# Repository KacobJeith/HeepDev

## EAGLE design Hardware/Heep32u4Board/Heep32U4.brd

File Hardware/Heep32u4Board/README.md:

# ATMega32u4 Board

### Description

This circuit board is designed to communicate with a Heep system without the need for any Arduino or Teensy circuit boards. It contains 2 relays, an ATMega32u4 Processor, and an ENC28J60 Ethernet Controller

### Schematic

### Layout

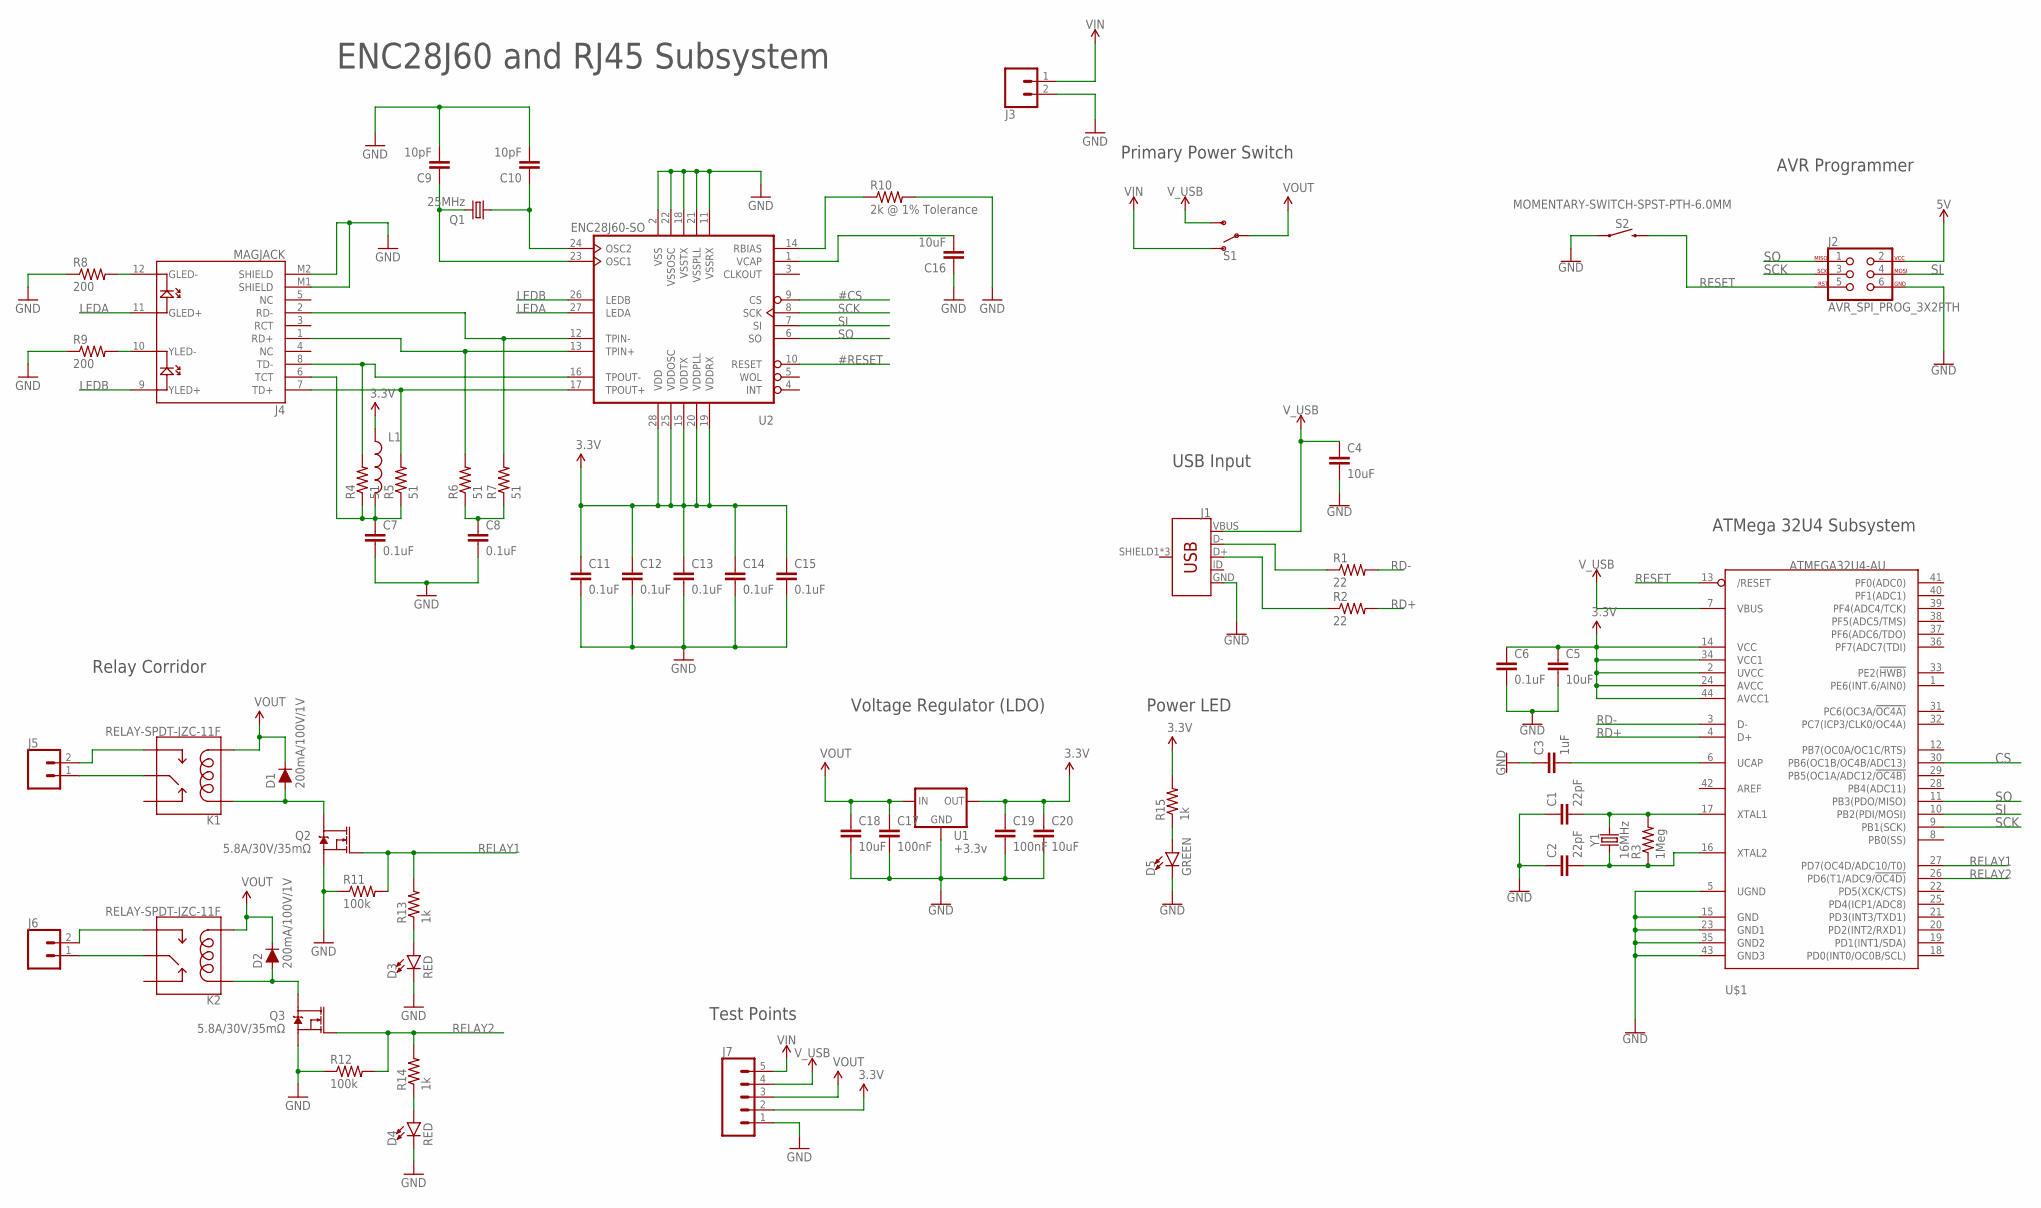
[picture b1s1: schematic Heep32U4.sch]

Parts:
C1, C2: 22pF; 0603-CAP
C3: 1uF; 0603-CAP
C4, C5, C16, C18, C20: 10uF; 0603-CAP
C6, C7, C8, C11, C12, C13, C14, C15: 0.1uF; 0603-CAP
C9, C10: 10pF; 0603-CAP
C17, C19: 100nF; 0603-CAP
D1, D2: 200mA/100V/1V; DIODE-1N4148
D3, D4: RED; LED-0603
D5: GREEN; LED-0603
J1: USB_MICRO-B_FEMALE-SMT; USB-B-MICRO-SMD
J2: AVR_SPI_PROG_3X2PTH; 2X3
J3: CONN_02; 1X02
J4: MAGJACK
J5, J6: CONN_025MM; SCREWTERMINAL-5MM-2
J7: CONN_05; 1X05
K1, K2: RELAY-SPDT-JZC-11F; RELAY-JZC
L1: INDUCTOR0603; 0603
Q1: 25MHz; SM49
Q2, Q3: 5.8A/30V/35mΩ; SOT23-3
R1, R2: 22; 0603-RES
R3: 1Meg; 0603-RES
R4, R5, R6, R7: 51; 0603-RES
R8, R9: 200; 0603-RES
R10: 2k @ 1% Tolerance; 0603-RES
R11, R12: 100k; 0603-RES
R13, R14, R15: 1k; 0603-RES
S1: SWITCH-SPDT-PTH-11.6X4.0MM; SWITCH_SPDT_PTH_11.6X4.0MM
S2: MOMENTARY-SWITCH-SPST-PTH-6.0MM; TACTILE_SWITCH_PTH_6.0MM
U1: +3.3v; TO-252
U2: ENC28J60-SO; SO28W
U$1: ATMEGA32U4-AU; TQFP44
Y1: 16MHz; HC49UP

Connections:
3.3V: C5.1, C6.1, C11.1, C12.1, C13.1, C14.1, C15.1, C19.1, C20.1, J7.2, L1.1, R15.2, U1.2 (OUT), U2.15 (VDDTX), U2.19 (VDDRX), U2.20 (VDDPLL), U2.25 (VDDOSC), U2.28 (VDD), U$1.2 (UVCC), U$1.14 (VCC), U$1.24 (AVCC), U$1.34 (VCC1), U$1.44 (AVCC1)
5V: J2.2
#CS: U2.9 (CS)
#RESET: U2.10 (RESET)
CS: U$1.30 (PB6(OC1B/OC4B/ADC13))
GND: C1.1, C2.1, C3.1, C4.2, C5.2, C6.2, C7.2, C8.2, C9.2, C10.2, C11.2, C12.2, C13.2, C14.2, C15.2, C16.1, C17.2, C18.2, C19.2, C20.2, D3.C, D4.C, D5.C, J1.GND, J2.6, J3.2, J4.M1 (SHIELD), J4.M2 (SHIELD), J7.1, Q2.2 (S), Q3.2 (S), R8.1, R9.1, R10.2, R11.1, R12.1, S2.1, U1.3 (GND), U2.2 (VSS), U2.11 (VSSRX), U2.18 (VSSTX), U2.21 (VSSPLL), U2.22 (VSSOSC), U$1.5 (UGND), U$1.15 (GND), U$1.23 (GND1), U$1.35 (GND2), U$1.43 (GND3)
LEDA: J4.11 (GLED+), U2.27 (LEDA)
LEDB: J4.9 (YLED+), U2.26 (LEDB)
unnamed: C3.2, U$1.6 (UCAP)
unnamed: J4.1 (RD+), R6.2, U2.13 (TPIN+)
unnamed: J1.D-, R1.1
unnamed: J1.D+, R2.1
unnamed: J4.2 (RD-), R7.2, U2.12 (TPIN-)
unnamed: J4.8 (TD-), R4.2, U2.16 (TPOUT-)
unnamed: J4.7 (TD+), R5.2, U2.17 (TPOUT+)
unnamed: C8.1, R6.1, R7.1
unnamed: C1.2, R3.2, U$1.17 (XTAL1), Y1.2
unnamed: C2.2, R3.1, U$1.16 (XTAL2), Y1.1
unnamed: C7.1, J4.6 (TCT), L1.2, R4.1, R5.1
unnamed: J4.10 (YLED-), R9.2
unnamed: J4.12 (GLED-), R8.2
unnamed: C9.1, Q1.2, U2.23 (OSC1)
unnamed: C10.1, Q1.1, U2.24 (OSC2)
unnamed: R10.1, U2.14 (RBIAS)
unnamed: C16.2, U2.1 (VCAP)
unnamed: J5.2, K1.3 (NO)
unnamed: J5.1, K1.4 (MAIN)
unnamed: J6.2, K2.3 (NO)
unnamed: J6.1, K2.4 (MAIN)
unnamed: D2.A, K2.5 (COIL1), Q3.3 (D)
unnamed: D1.A, K1.5 (COIL1), Q2.3 (D)
unnamed: D5.A, R15.1
unnamed: D4.A, R14.1
unnamed: D3.A, R13.1
RD+: R2.2, U$1.4 (D+)
RD-: R1.2, U$1.3 (D-)
RELAY1: Q2.1 (G), R11.2, R13.2, U$1.27 (PD7(OC4D/ADC10/T0))
RELAY2: Q3.1 (G), R12.2, R14.2, U$1.26 (PD6(T1/ADC9/!OC4D))
RESET: J2.5, S2.3 (2), U$1.13 (/RESET)
SCK: J2.3, U2.8 (SCK), U$1.9 (PB1(SCK))
SI: J2.4, U2.7 (SI), U$1.10 (PB2(PDI/MOSI))
SO: J2.1, U2.6 (SO), U$1.11 (PB3(PDO/MISO))
VIN: J3.1, J7.5, S1.1 (O)
VOUT: C17.1, C18.1, D1.C, D2.C, J7.3, K1.1 (COIL2), K2.1 (COIL2), S1.2, U1.1 (IN)
V_USB: C4.1, J1.VBUS, J7.4, S1.3 (S), U$1.7 (VBUS)

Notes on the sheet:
USB Input
Primary Power Switch
ATMega 32U4 Subsystem
AVR Programmer
ENC28J60 and RJ45 Subsystem
Voltage Regulator (LDO)
Relay Corridor
Test Points
Power LED

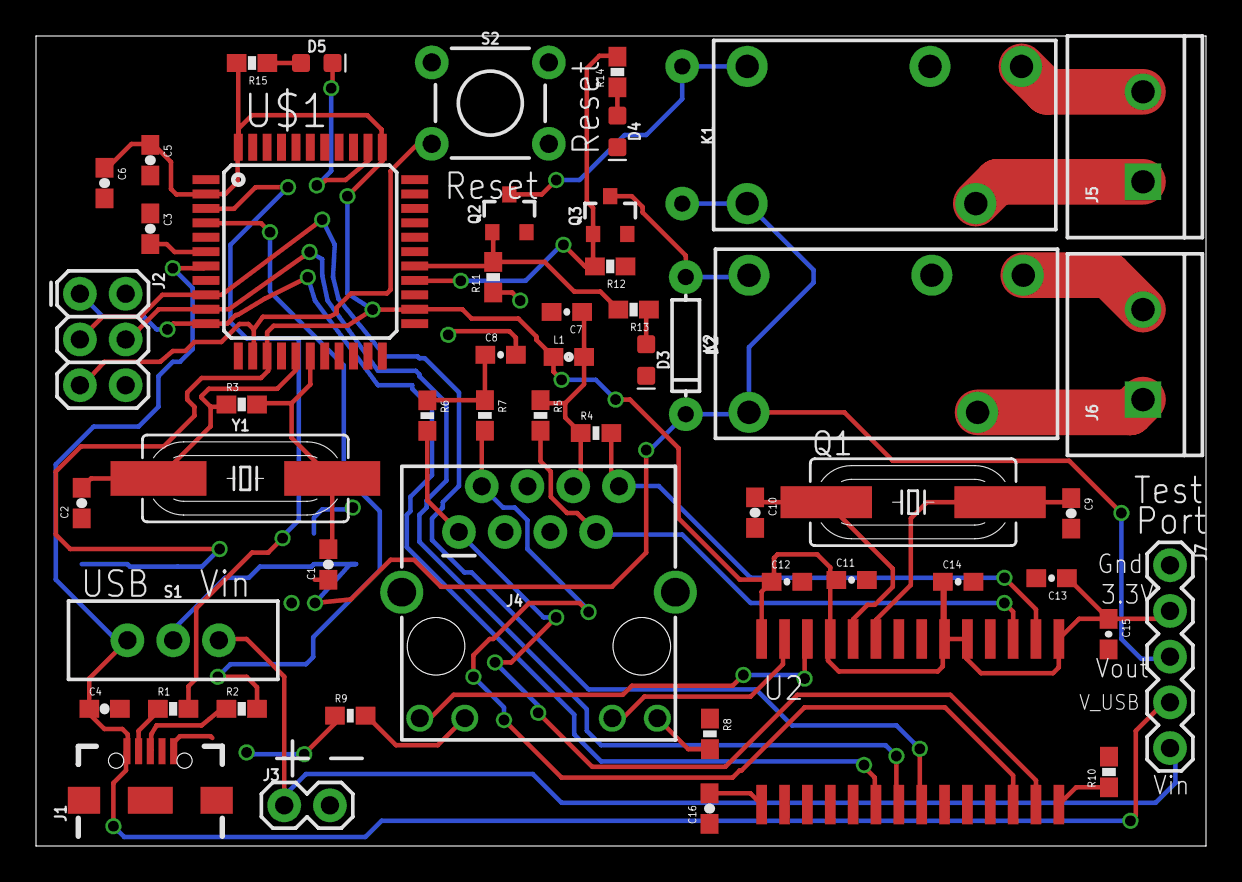
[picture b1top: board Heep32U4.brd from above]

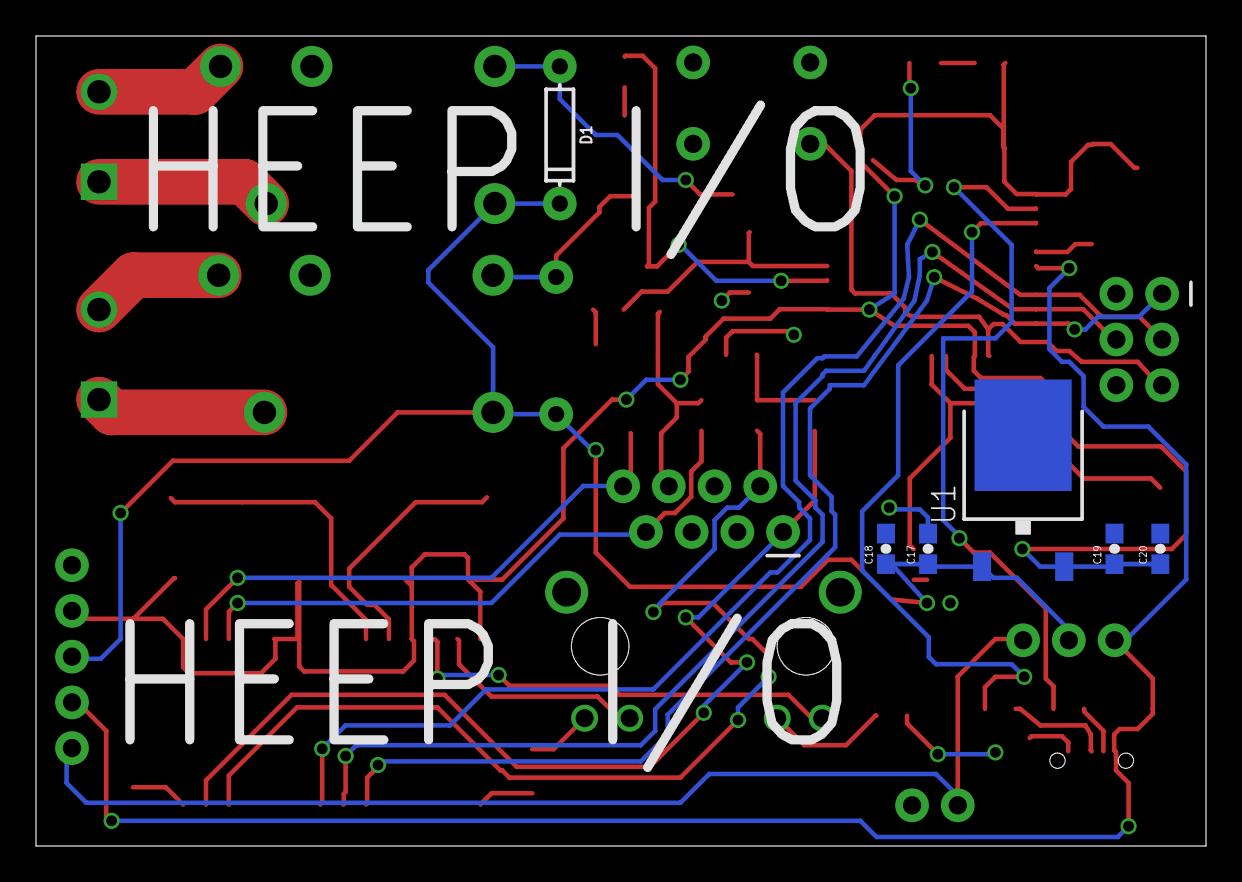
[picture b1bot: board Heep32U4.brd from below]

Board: 2 copper layers, 65.0 x 45.0 mm, 59 parts (6 on the bottom side), 41 nets.

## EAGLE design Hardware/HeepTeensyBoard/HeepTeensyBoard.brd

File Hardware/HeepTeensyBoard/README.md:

# Heep Teensy Board

### Description

This circuit board is an inexpensive way to get a Teensy to communicate over ethernet. It uses the ENC28J60 chip and a Teensy.

### Schematic

### Layout

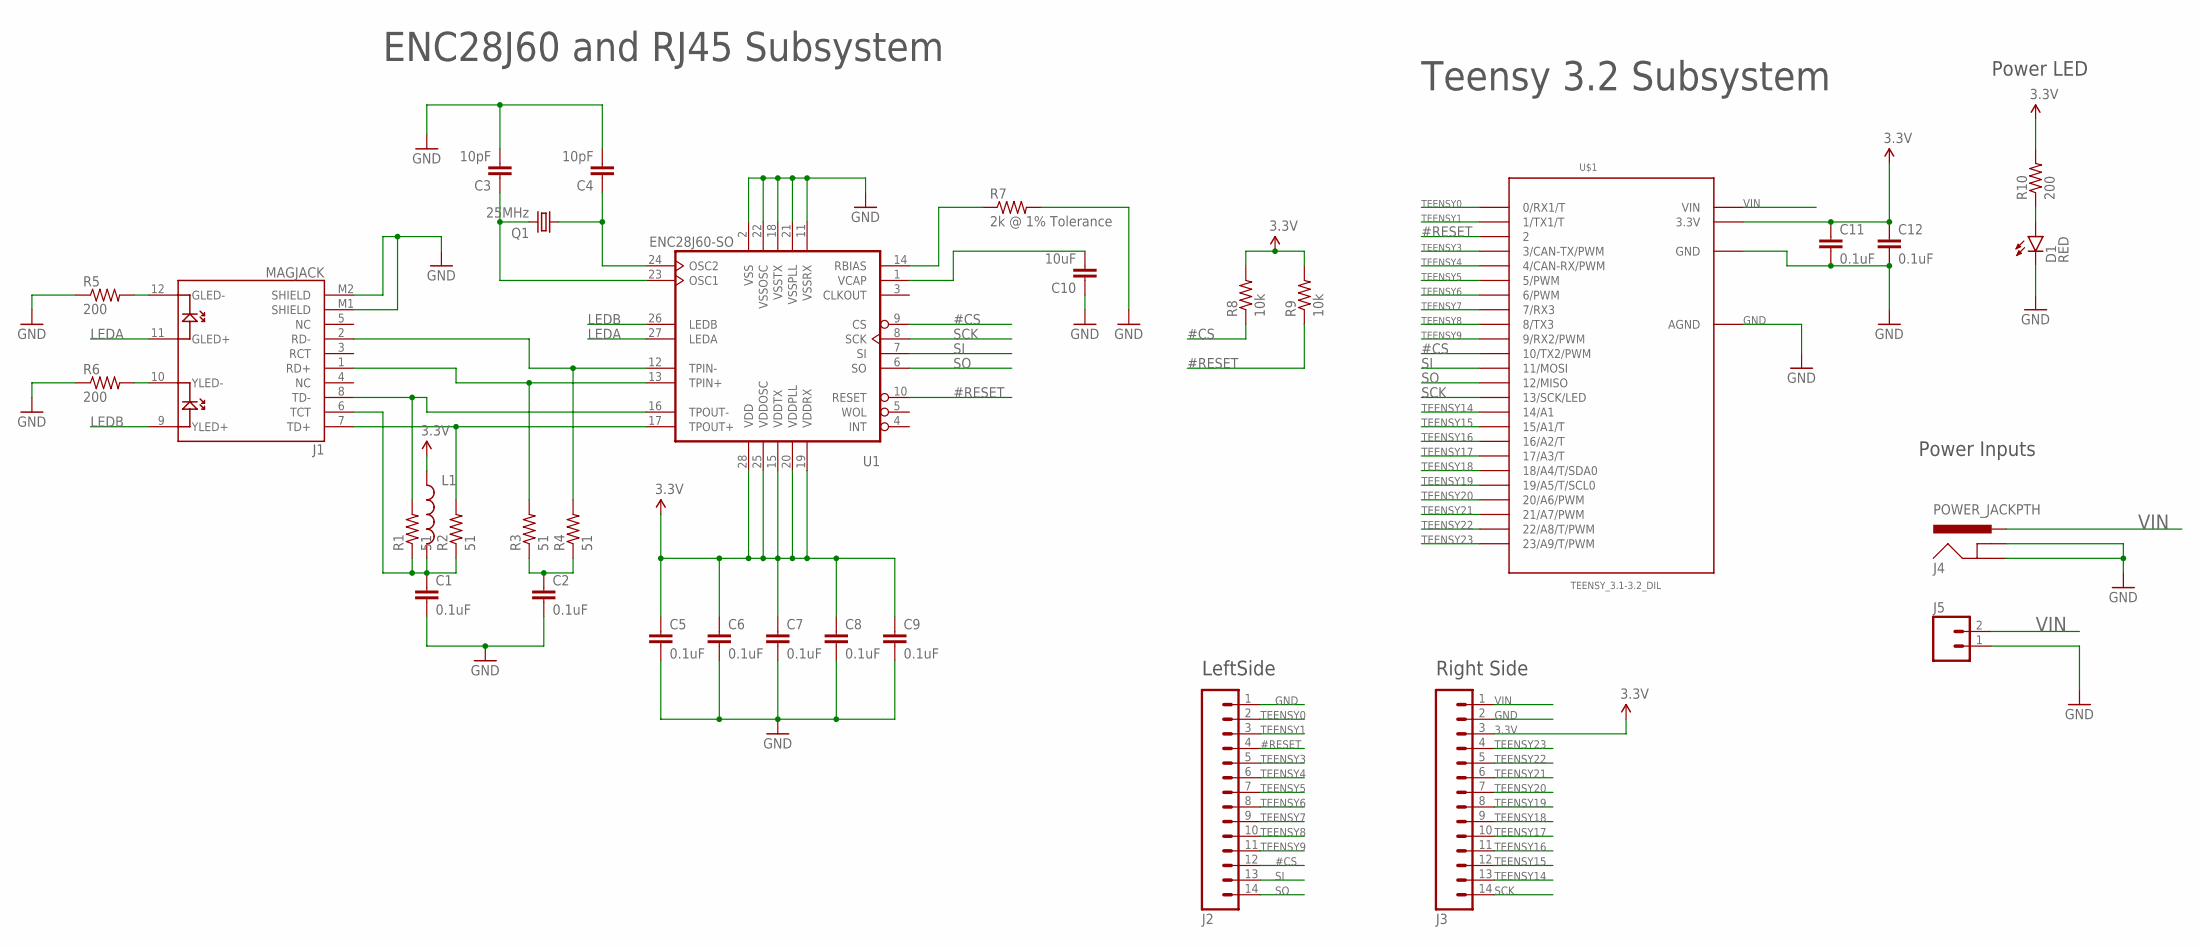
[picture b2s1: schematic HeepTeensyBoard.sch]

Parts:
C1, C2, C5, C6, C7, C8, C9, C11, C12: 0.1uF; 0603-CAP
C3, C4: 10pF; 0603-CAP
C10: 10uF; 0603-CAP
D1: RED; LED-0603
J1: MAGJACK
J2, J3: M14; 1X14
J4: POWER_JACKPTH; POWER_JACK_PTH
J5: M02PTH; 1X02
L1: INDUCTOR0603; 0603
Q1: 25MHz; SM49
R1, R2, R3, R4: 51; 0603-RES
R5, R6, R10: 200; 0603-RES
R7: 2k @ 1% Tolerance; 0603-RES
R8, R9: 10k; 0603-RES
U1: ENC28J60-SO; SO28W
U$1: TEENSY_3.1-3.2_DIL; TEENSY_3.0-3.2&LC_DIL

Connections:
3.3V: C5.1, C6.1, C7.1, C8.1, C9.1, C11.1, C12.1, J3.3, L1.1, R8.2, R9.2, R10.2, U1.15 (VDDTX), U1.19 (VDDRX), U1.20 (VDDPLL), U1.25 (VDDOSC), U1.28 (VDD), U$1.3.3V
#CS: J2.12, R8.1, U1.9 (CS), U$1.10 (10/TX2/PWM)
#RESET: J2.4, R9.1, U1.10 (RESET), U$1.2
GND: C1.2, C2.2, C3.2, C4.2, C5.2, C6.2, C7.2, C8.2, C9.2, C10.1, C11.2, C12.2, D1.C, J1.M1 (SHIELD), J1.M2 (SHIELD), J2.1, J3.2, J4.GND, J4.GNDBREAK, J5.1, R5.1, R6.1, R7.2, U1.2 (VSS), U1.11 (VSSRX), U1.18 (VSSTX), U1.21 (VSSPLL), U1.22 (VSSOSC), U$1.AGND, U$1.GND
LEDA: J1.11 (GLED+), U1.27 (LEDA)
LEDB: J1.9 (YLED+), U1.26 (LEDB)
unnamed: J1.1 (RD+), R3.2, U1.13 (TPIN+)
unnamed: J1.2 (RD-), R4.2, U1.12 (TPIN-)
unnamed: J1.8 (TD-), R1.2, U1.16 (TPOUT-)
unnamed: J1.7 (TD+), R2.2, U1.17 (TPOUT+)
unnamed: C2.1, R3.1, R4.1
unnamed: J1.10 (YLED-), R6.2
unnamed: C1.1, J1.6 (TCT), L1.2, R1.1, R2.1
unnamed: D1.A, R10.1
unnamed: J1.12 (GLED-), R5.2
unnamed: C3.1, Q1.2, U1.23 (OSC1)
unnamed: C4.1, Q1.1, U1.24 (OSC2)
unnamed: R7.1, U1.14 (RBIAS)
unnamed: C10.2, U1.1 (VCAP)
SCK: J3.14, U1.8 (SCK), U$1.13 (13/SCK/LED)
SI: J2.13, U1.7 (SI), U$1.11 (11/MOSI)
SO: J2.14, U1.6 (SO), U$1.12 (12/MISO)
TEENSY0: J2.2, U$1.0 (0/RX1/T)
TEENSY1: J2.3, U$1.1 (1/TX1/T)
TEENSY3: J2.5, U$1.3 (3/CAN-TX/PWM)
TEENSY4: J2.6, U$1.4 (4/CAN-RX/PWM)
TEENSY5: J2.7, U$1.5 (5/PWM)
TEENSY6: J2.8, U$1.6 (6/PWM)
TEENSY7: J2.9, U$1.7 (7/RX3)
TEENSY8: J2.10, U$1.8 (8/TX3)
TEENSY9: J2.11, U$1.9 (9/RX2/PWM)
TEENSY14: J3.13, U$1.14/A0 (14/A1)
TEENSY15: J3.12, U$1.15/A1 (15/A1/T)
TEENSY16: J3.11, U$1.16/A2 (16/A2/T)
TEENSY17: J3.10, U$1.17/A3 (17/A3/T)
TEENSY18: J3.9, U$1.18/A4 (18/A4/T/SDA0)
TEENSY19: J3.8, U$1.19/A5 (19/A5/T/SCL0)
TEENSY20: J3.7, U$1.20/A6 (20/A6/PWM)
TEENSY21: J3.6, U$1.21/A7 (21/A7/PWM)
TEENSY22: J3.5, U$1.22/A8 (22/A8/T/PWM)
TEENSY23: J3.4, U$1.23/A9 (23/A9/T/PWM)
VIN: J3.1, J4.PWR, J5.2, U$1.VIN

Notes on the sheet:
ENC28J60 and RJ45 Subsystem
Teensy 3.2 Subsystem
LeftSide
Right Side
Power LED
Power Inputs

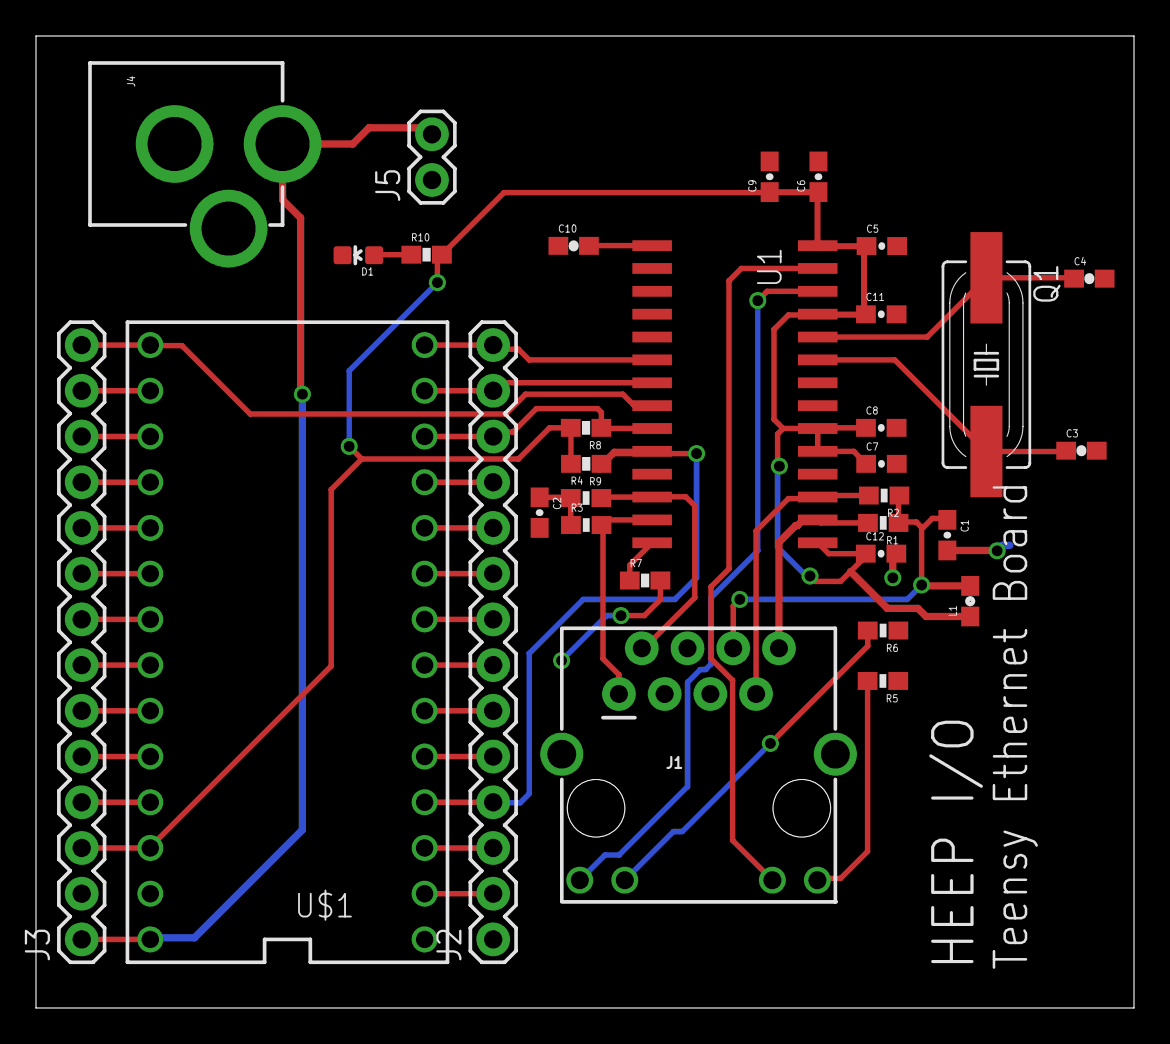
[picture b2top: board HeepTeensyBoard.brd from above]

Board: 2 copper layers, 61.0 x 54.0 mm, 32 parts (0 on the bottom side), 42 nets.

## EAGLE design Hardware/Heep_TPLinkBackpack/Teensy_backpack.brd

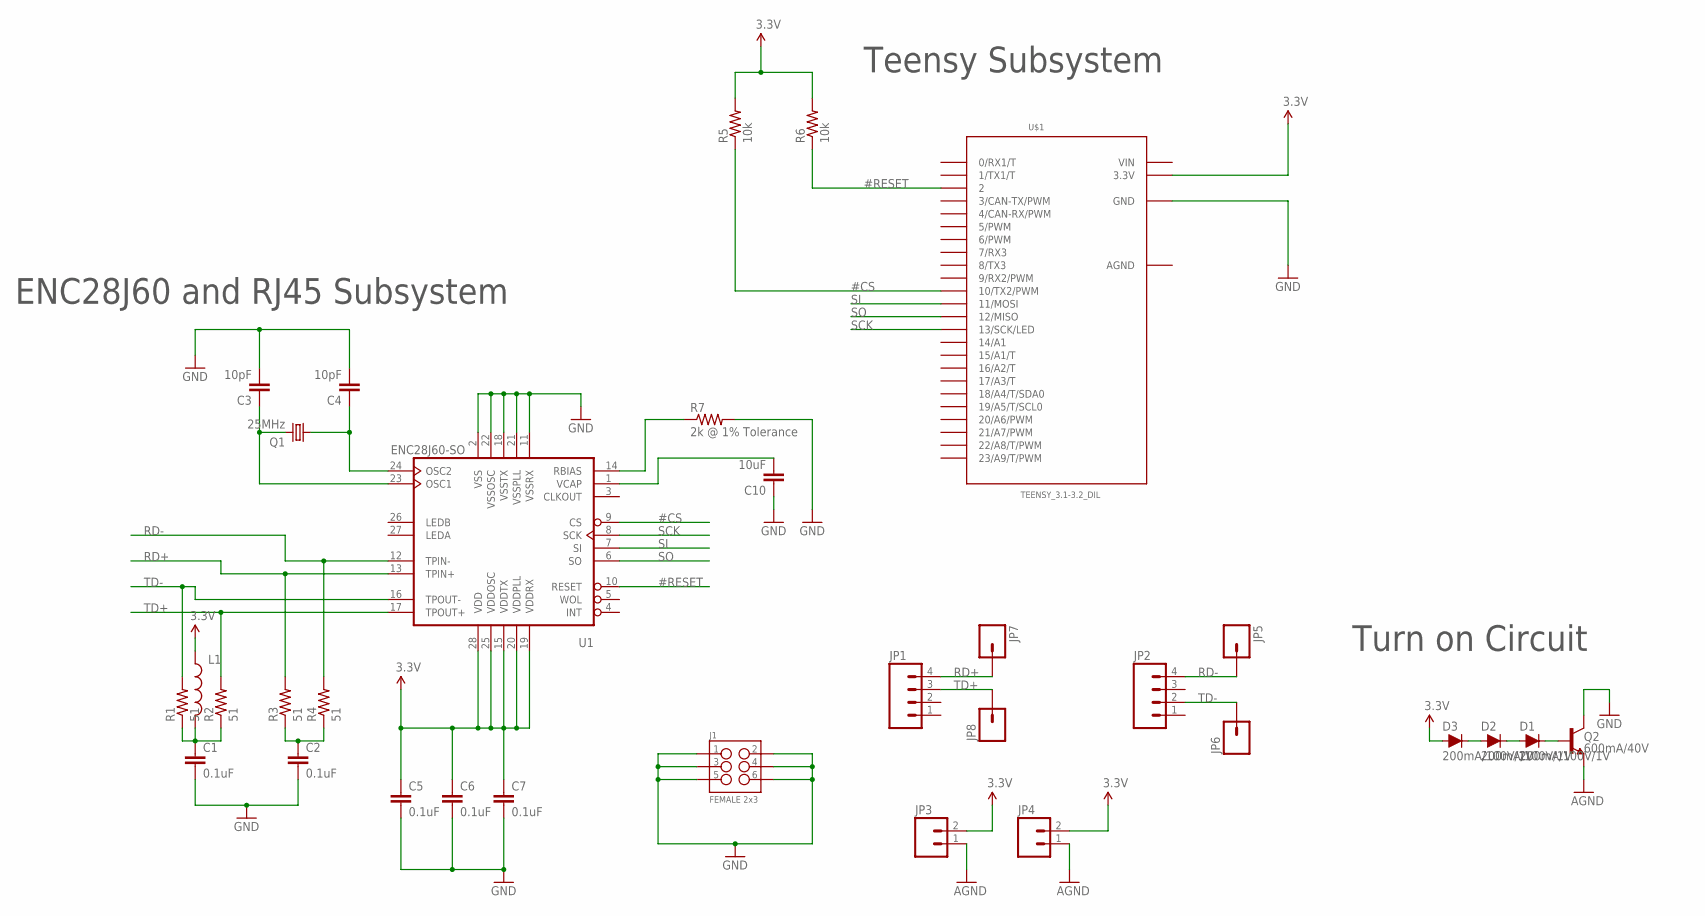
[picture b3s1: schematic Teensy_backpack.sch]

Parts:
C1, C2, C5, C6, C7: 0.1uF; 0603-CAP
C3, C4: 10pF; 0603-CAP
C10: 10uF; 0603-CAP
D1, D2, D3: 200mA/100V/1V; DIODE-1N4148
J1: FEMALE 2x3; 2X3
JP1, JP2: M04NO_SILK_ALL_ROUND; 1X04_NO_SILK_ALL_ROUND
JP3, JP4: M021X02_NO_SILK; 1X02_NO_SILK
JP5, JP6, JP7, JP8: M01NOSILK-KIT; 1X01NS-KIT
L1: INDUCTOR0603; 0603
Q1: 25MHz; SM49
Q2: 600mA/40V; TO-92
R1, R2, R3, R4: 51; 0603-RES
R5, R6: 10k; 0603-RES
R7: 2k @ 1% Tolerance; 0603-RES
U1: ENC28J60-SO; SO28W
U$1: TEENSY_3.1-3.2_DIL; TEENSY_3.0-3.2&LC_DIL

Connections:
3.3V: C5.1, C6.1, C7.1, D3.A, JP3.2, JP4.2, L1.1, R5.2, R6.2, U1.15 (VDDTX), U1.19 (VDDRX), U1.20 (VDDPLL), U1.25 (VDDOSC), U1.28 (VDD), U$1.3.3V
#CS: R5.1, U1.9 (CS), U$1.10 (10/TX2/PWM)
#RESET: R6.1, U1.10 (RESET), U$1.2
AGND: JP3.1, JP4.1, Q2.3 (E), U$1.AGND
GND: C1.2, C2.2, C3.2, C4.2, C5.2, C6.2, C7.2, C10.1, J1.1, J1.2, J1.3, J1.4, J1.5, J1.6, Q2.1 (C), R7.2, U1.2 (VSS), U1.11 (VSSRX), U1.18 (VSSTX), U1.21 (VSSPLL), U1.22 (VSSOSC), U$1.GND
unnamed: D1.A, D2.C
unnamed: D1.C, Q2.2 (B)
unnamed: D2.A, D3.C
unnamed: C2.1, R3.1, R4.1
unnamed: C1.1, L1.2, R1.1, R2.1
unnamed: C3.1, Q1.2, U1.23 (OSC1)
unnamed: C4.1, Q1.1, U1.24 (OSC2)
unnamed: R7.1, U1.14 (RBIAS)
unnamed: C10.2, U1.1 (VCAP)
RD+: JP1.4, JP7.1, R3.2, U1.13 (TPIN+)
RD-: JP2.4, JP5.1, R4.2, U1.12 (TPIN-)
SCK: U1.8 (SCK), U$1.13 (13/SCK/LED)
SI: U1.7 (SI), U$1.11 (11/MOSI)
SO: U1.6 (SO), U$1.12 (12/MISO)
TD+: JP1.3, JP8.1, R2.2, U1.17 (TPOUT+)
TD-: JP2.2, JP6.1, R1.2, U1.16 (TPOUT-)
VIN: U$1.VIN

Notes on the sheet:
ENC28J60 and RJ45 Subsystem
Teensy Subsystem
Turn on Circuit

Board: 2 copper layers, 32 parts (0 on the bottom side), 21 nets, no tracks yet.

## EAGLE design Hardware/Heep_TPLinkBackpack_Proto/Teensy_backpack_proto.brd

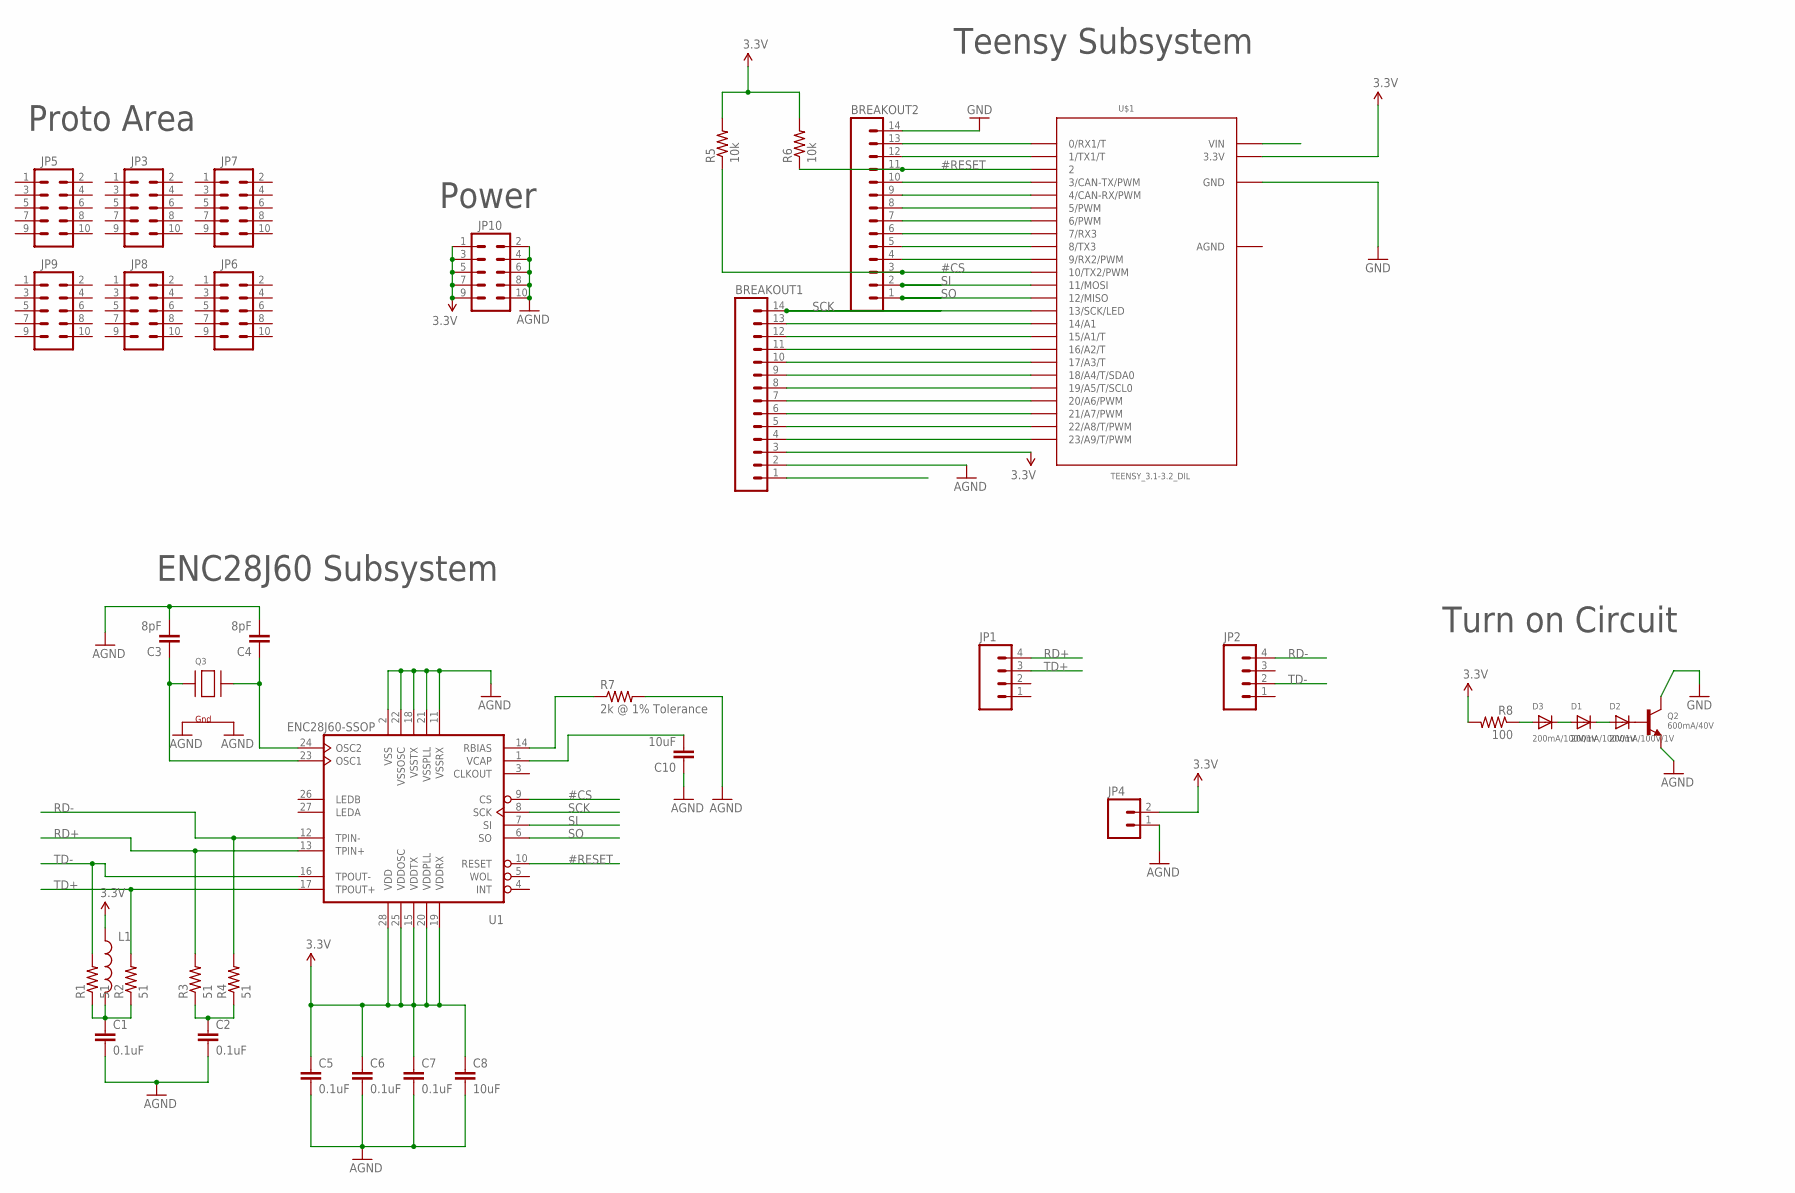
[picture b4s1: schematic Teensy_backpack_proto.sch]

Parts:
BREAKOUT1, BREAKOUT2: M14; 1X14
C1, C2, C5, C6, C7: 0.1uF; 0603-CAP
C3, C4: 8pF; 0603-CAP
C8, C10: 10uF; 0603-CAP
D1, D2, D3: 200mA/100V/1V; SOD-123
JP1, JP2: M04NO_SILK_ALL_ROUND; 1X04_NO_SILK_ALL_ROUND
JP3, JP5, JP6, JP7, JP8, JP9, JP10: M05X2NO_SILK; 2X5_NOSILK
JP4: M021X02_NO_SILK; 1X02_NO_SILK
L1: INDUCTOR0603; 0603
Q2: 600mA/40V; SOT23-R
Q3: XTAL-4-3225; NX3225
R1, R2, R3, R4: 51; 0603-RES
R5, R6: 10k; 0603-RES
R7: 2k @ 1% Tolerance; 0603-RES
R8: 100; 0603-RES
U1: ENC28J60-SSOP; SSOP28
U$1: TEENSY_3.1-3.2_DIL; TEENSY_3.0-3.2&LC_DIL

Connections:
3.3V: BREAKOUT1.3, C5.1, C6.1, C7.1, C8.1, JP4.2, JP10.1, JP10.3, JP10.5, JP10.7, JP10.9, L1.1, R5.2, R6.2, R8.2, U1.15 (VDDTX), U1.19 (VDDRX), U1.20 (VDDPLL), U1.25 (VDDOSC), U1.28 (VDD), U$1.3.3V
#CS: BREAKOUT2.3, R5.1, U1.9 (CS), U$1.10 (10/TX2/PWM)
#RESET: BREAKOUT2.11, R6.1, U1.10 (RESET), U$1.2
AGND: BREAKOUT1.2, C1.2, C2.2, C3.2, C4.2, C5.2, C6.2, C7.2, C8.2, C10.1, JP4.1, JP10.2, JP10.4, JP10.6, JP10.8, JP10.10, Q2.2 (E), Q3.2 (G2), Q3.4 (G1), R7.2, U1.2 (VSS), U1.11 (VSSRX), U1.18 (VSSTX), U1.21 (VSSPLL), U1.22 (VSSOSC), U$1.AGND
GND: BREAKOUT2.14, Q2.3 (C), U$1.GND
unnamed: D1.C, D2.A
unnamed: D2.C, Q2.1 (B)
unnamed: D1.A, D3.C
unnamed: D3.A, R8.1
unnamed: C2.1, R3.1, R4.1
unnamed: BREAKOUT2.4, U$1.9 (9/RX2/PWM)
unnamed: C1.1, L1.2, R1.1, R2.1
unnamed: BREAKOUT2.5, U$1.8 (8/TX3)
unnamed: BREAKOUT2.6, U$1.7 (7/RX3)
unnamed: BREAKOUT2.7, U$1.6 (6/PWM)
unnamed: BREAKOUT2.8, U$1.5 (5/PWM)
unnamed: C3.1, Q3.1 (X1), U1.23 (OSC1)
unnamed: C4.1, Q3.3 (X2), U1.24 (OSC2)
unnamed: BREAKOUT2.9, U$1.4 (4/CAN-RX/PWM)
unnamed: R7.1, U1.14 (RBIAS)
unnamed: BREAKOUT2.10, U$1.3 (3/CAN-TX/PWM)
unnamed: C10.2, U1.1 (VCAP)
unnamed: BREAKOUT2.12, U$1.1 (1/TX1/T)
unnamed: BREAKOUT2.13, U$1.0 (0/RX1/T)
unnamed: BREAKOUT1.4, U$1.23/A9 (23/A9/T/PWM)
unnamed: BREAKOUT1.5, U$1.22/A8 (22/A8/T/PWM)
unnamed: BREAKOUT1.6, U$1.21/A7 (21/A7/PWM)
unnamed: BREAKOUT1.7, U$1.20/A6 (20/A6/PWM)
unnamed: BREAKOUT1.8, U$1.19/A5 (19/A5/T/SCL0)
unnamed: BREAKOUT1.9, U$1.18/A4 (18/A4/T/SDA0)
unnamed: BREAKOUT1.10, U$1.17/A3 (17/A3/T)
unnamed: BREAKOUT1.11, U$1.16/A2 (16/A2/T)
unnamed: BREAKOUT1.12, U$1.15/A1 (15/A1/T)
unnamed: BREAKOUT1.13, U$1.14/A0 (14/A1)
RD+: JP1.4, R3.2, U1.13 (TPIN+)
RD-: JP2.4, R4.2, U1.12 (TPIN-)
SCK: BREAKOUT1.14, U1.8 (SCK), U$1.13 (13/SCK/LED)
SI: BREAKOUT2.2, U1.7 (SI), U$1.11 (11/MOSI)
SO: BREAKOUT2.1, U1.6 (SO), U$1.12 (12/MISO)
TD+: JP1.3, R2.2, U1.17 (TPOUT+)
TD-: JP2.2, R1.2, U1.16 (TPOUT-)
TEENSY_VIN: BREAKOUT1.1, U$1.VIN

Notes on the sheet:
ENC28J60 Subsystem
Teensy Subsystem
Turn on Circuit
Proto Area
Power

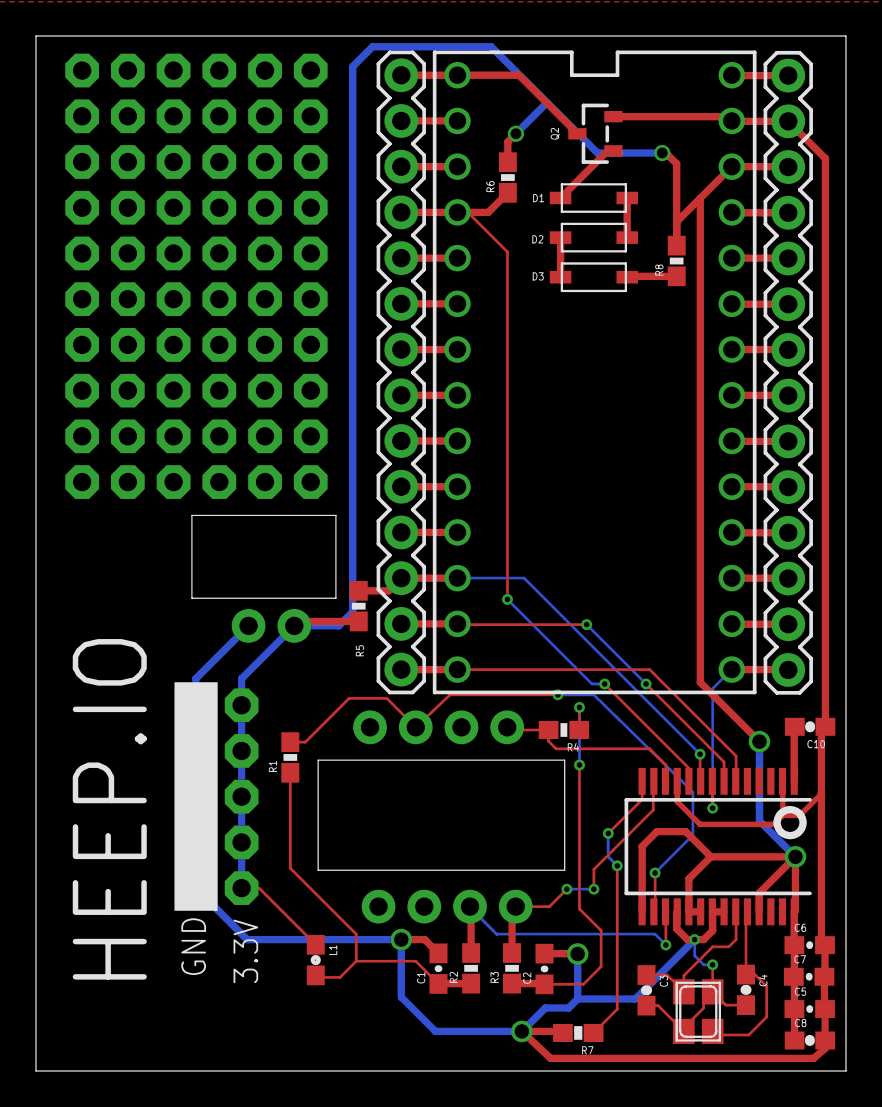
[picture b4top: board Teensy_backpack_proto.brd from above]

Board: 2 copper layers, 45.0 x 57.5 mm, 37 parts (0 on the bottom side), 42 nets.

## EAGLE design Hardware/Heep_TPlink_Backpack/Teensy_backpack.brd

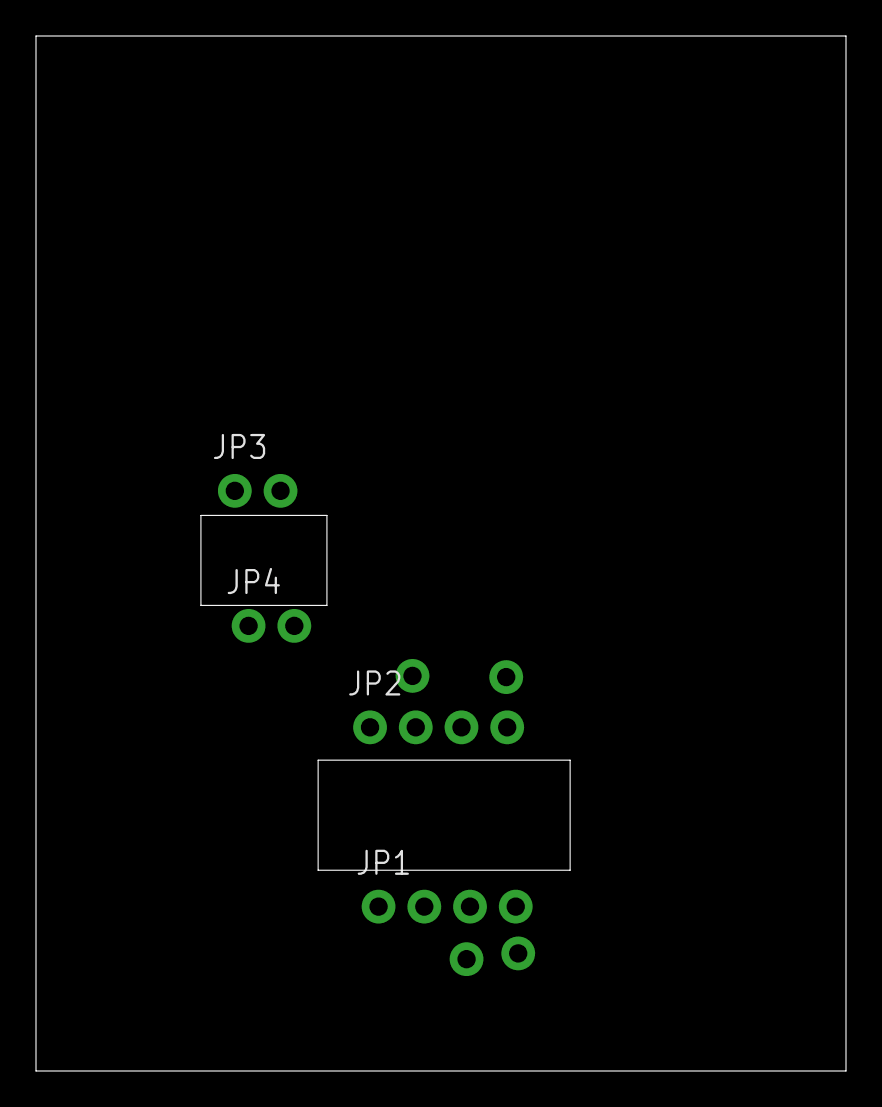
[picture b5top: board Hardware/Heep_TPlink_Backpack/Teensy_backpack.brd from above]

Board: 2 copper layers, 45.0 x 57.5 mm, 8 parts (0 on the bottom side), 6 nets, no tracks yet.

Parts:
JP1, JP2: 1X04_NO_SILK_ALL_ROUND
JP3, JP4: 1X02_NO_SILK
JP5, JP6, JP7, JP8: 1X01NS-KIT

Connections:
+3V3: JP3.2, JP4.2
GND: JP3.1, JP4.1
RX+: JP1.4, JP7.1
RX-: JP2.4, JP5.1
TX+: JP1.3, JP8.1
TX-: JP2.2, JP6.1

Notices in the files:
parts and their libraries:
SparkFun-Passives: Licensing: Creative Commons ShareAlike 4.0 International - https://creativecommons.org/licenses/by-sa/4.0
microbuilder: This work is placed in the public domain, and may be freely used for commercial and non-commercial work with the following conditions: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
